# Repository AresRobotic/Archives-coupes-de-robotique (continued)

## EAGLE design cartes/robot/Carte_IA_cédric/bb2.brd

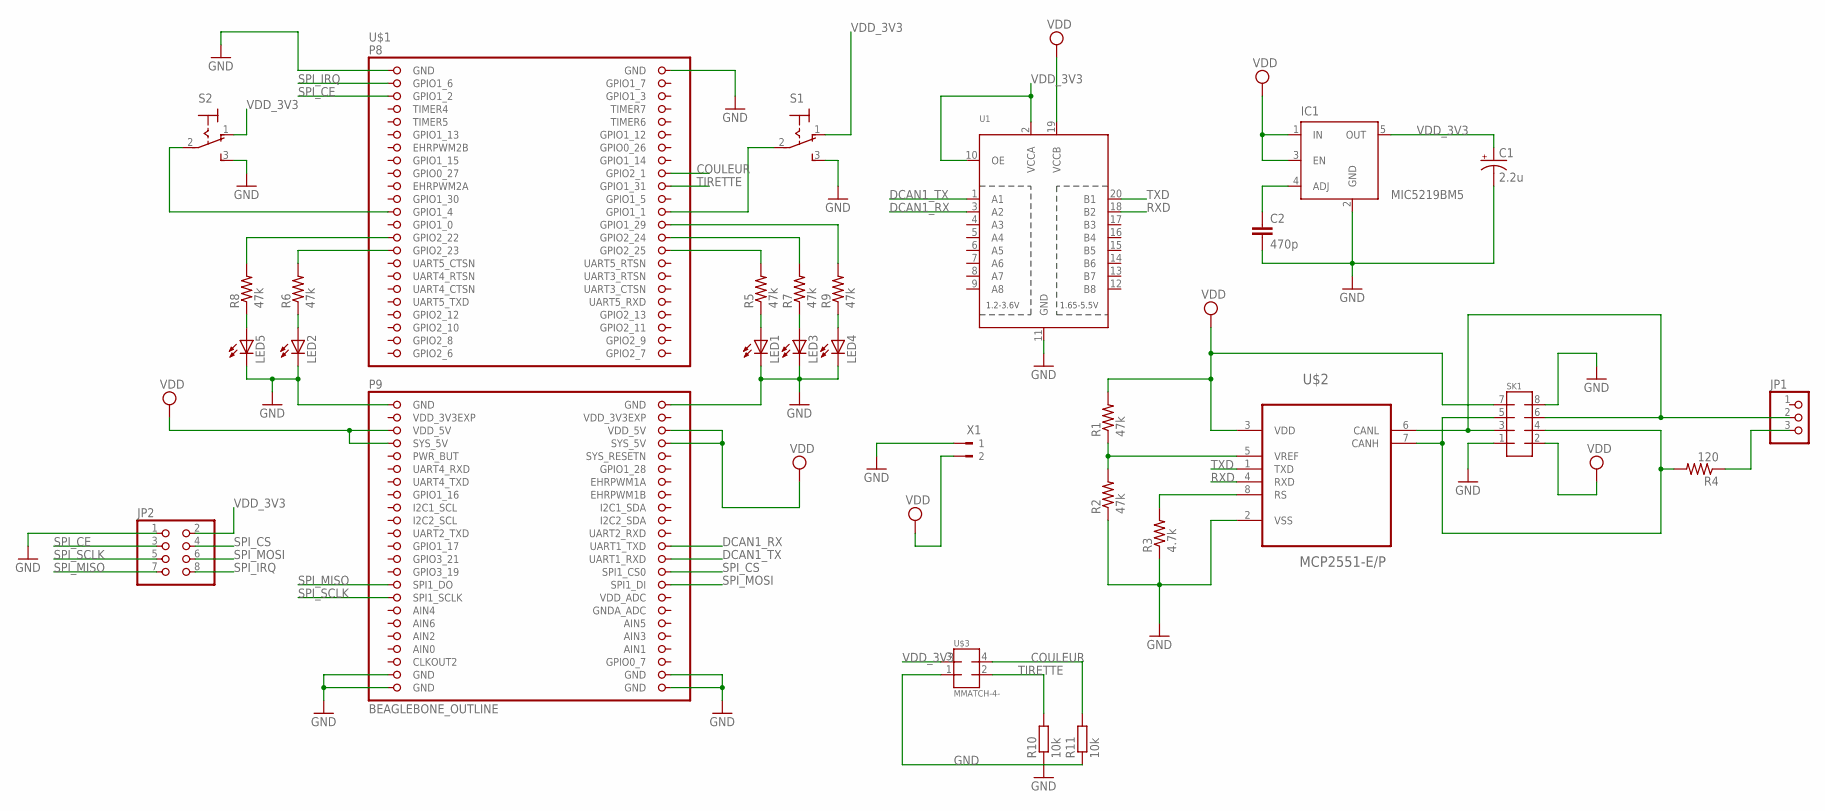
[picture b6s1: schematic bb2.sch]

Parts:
C1: 2.2u; E5-4
C2: 470p; C025-040X050
IC1: MIC5219BM5; SOT23-5
JP1: PINHD-1X3; 1X03
JP2: PINHD-2X4; 2X04
LED1, LED2, LED3, LED4, LED5: LED5MM
R1, R2, R5, R6, R7, R8, R9: 47k; 0207/9
R3: 4.7k; 0207/9
R4: 120; 0207/9
R10, R11: 10k; R0805
S1, S2: 320-916
SK1: MMATCH-8-PTH; AMP-215079-8
U1: TXB0108PWR; TSSOP20
U$1: BEAGLEBONE_OUTLINE; BEAGLEBONE_SHIELD
U$2: MCP2551-E/P; DIP254P762X432-8
U$3: MMATCH-4-; AMP-215079-4
X1: 180G-2

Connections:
AIN0: U$1.85 (AIN0)
COULEUR: R11.2, U$1.18 (GPIO2_1), U$3.4 (8)
DCAN1_RX: U1.3 (A2), U$1.70 (UART1_TXD)
DCAN1_TX: U1.1 (A1), U$1.72 (UART1_RXD)
GND: C1.-, C2.2, IC1.2 (GND), JP2.1, LED1.K (C), LED2.K (C), LED3.K (C), LED4.K (C), LED5.K (C), R2.1, R3.1, R10.1, R11.1, S1.3 (S), S2.3 (S), SK1.1, SK1.8, U1.11 (GND), U$1.1 (GND), U$1.2 (GND), U$1.47 (GND), U$1.48 (GND), U$1.89 (GND), U$1.90 (GND), U$1.91 (GND), U$1.92 (GND), U$2.2 (VSS), U$3.1 (5), X1.1
unnamed: R1.1, R2.2, U$2.5 (VREF)
unnamed: JP1.3, R4.1
unnamed: R3.2, U$2.8 (RS)
unnamed: C2.1, IC1.4 (ADJ)
unnamed: R5.2, U$1.30 (GPIO2_25)
unnamed: R6.2, U$1.29 (GPIO2_23)
unnamed: R7.2, U$1.28 (GPIO2_24)
unnamed: R9.2, U$1.26 (GPIO1_29)
unnamed: LED5.A, R8.1
unnamed: S1.2, U$1.24 (GPIO1_1)
unnamed: S2.2, U$1.23 (GPIO1_4)
unnamed: R8.2, U$1.27 (GPIO2_22)
unnamed: JP1.2, SK1.3, SK1.6, U$2.6 (CANL)
unnamed: R4.2, SK1.4, SK1.5, U$2.7 (CANH)
unnamed: LED2.A, R6.1
unnamed: LED1.A, R5.1
unnamed: LED3.A, R7.1
unnamed: LED4.A, R9.1
RXD: U1.18 (B2), U$2.4 (RXD)
SPI_CE: JP2.3, U$1.5 (GPIO1_2)
SPI_CS: JP2.4, U$1.74 (SPI1_CS0)
SPI_IRQ: JP2.8, U$1.3 (GPIO1_6)
SPI_MISO: JP2.7, U$1.75 (SPI1_DO)
SPI_MOSI: JP2.6, U$1.76 (SPI1_DI)
SPI_SCLK: JP2.5, U$1.77 (SPI1_SCLK)
TIRETTE: R10.2, U$1.20 (GPIO1_31), U$3.2 (6)
TXD: U1.20 (B1), U$2.1 (TXD)
VDD: IC1.1 (IN), IC1.3 (EN), R1.2, SK1.2, SK1.7, U1.19 (VCCB), U$1.51 (VDD_5V), U$1.52 (VDD_5V), U$1.53 (SYS_5V), U$1.54 (SYS_5V), U$2.3 (VDD), X1.2
VDD_3V3: C1.+, IC1.5 (OUT), JP2.2, S1.1 (O), S2.1 (O), U1.2 (VCCA), U1.10 (OE), U$3.3 (7)
VDD_3V3EXP: U$1.49 (VDD_3V3EXP), U$1.50 (VDD_3V3EXP)

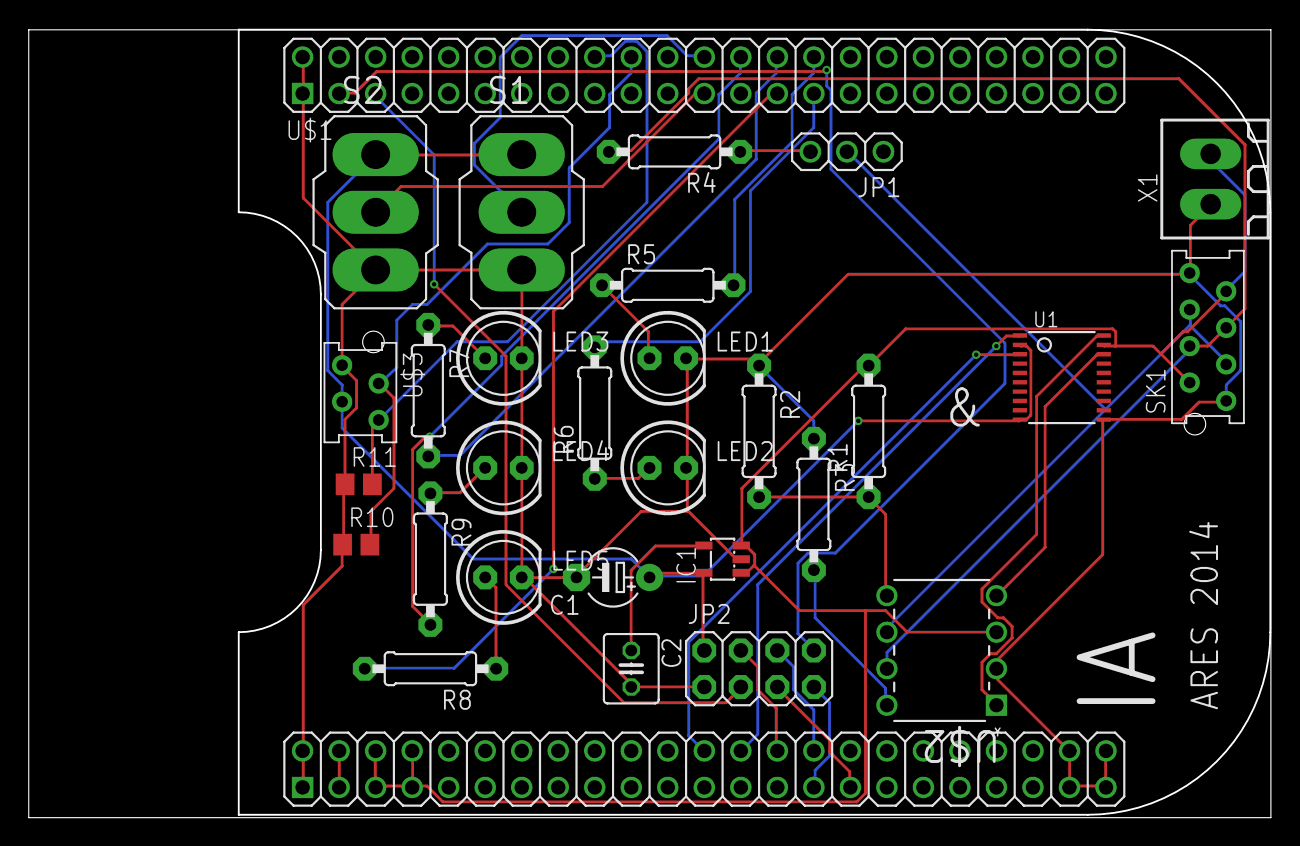
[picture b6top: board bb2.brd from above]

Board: 2 copper layers, 86.3 x 54.7 mm, 29 parts (0 on the bottom side), 34 nets.

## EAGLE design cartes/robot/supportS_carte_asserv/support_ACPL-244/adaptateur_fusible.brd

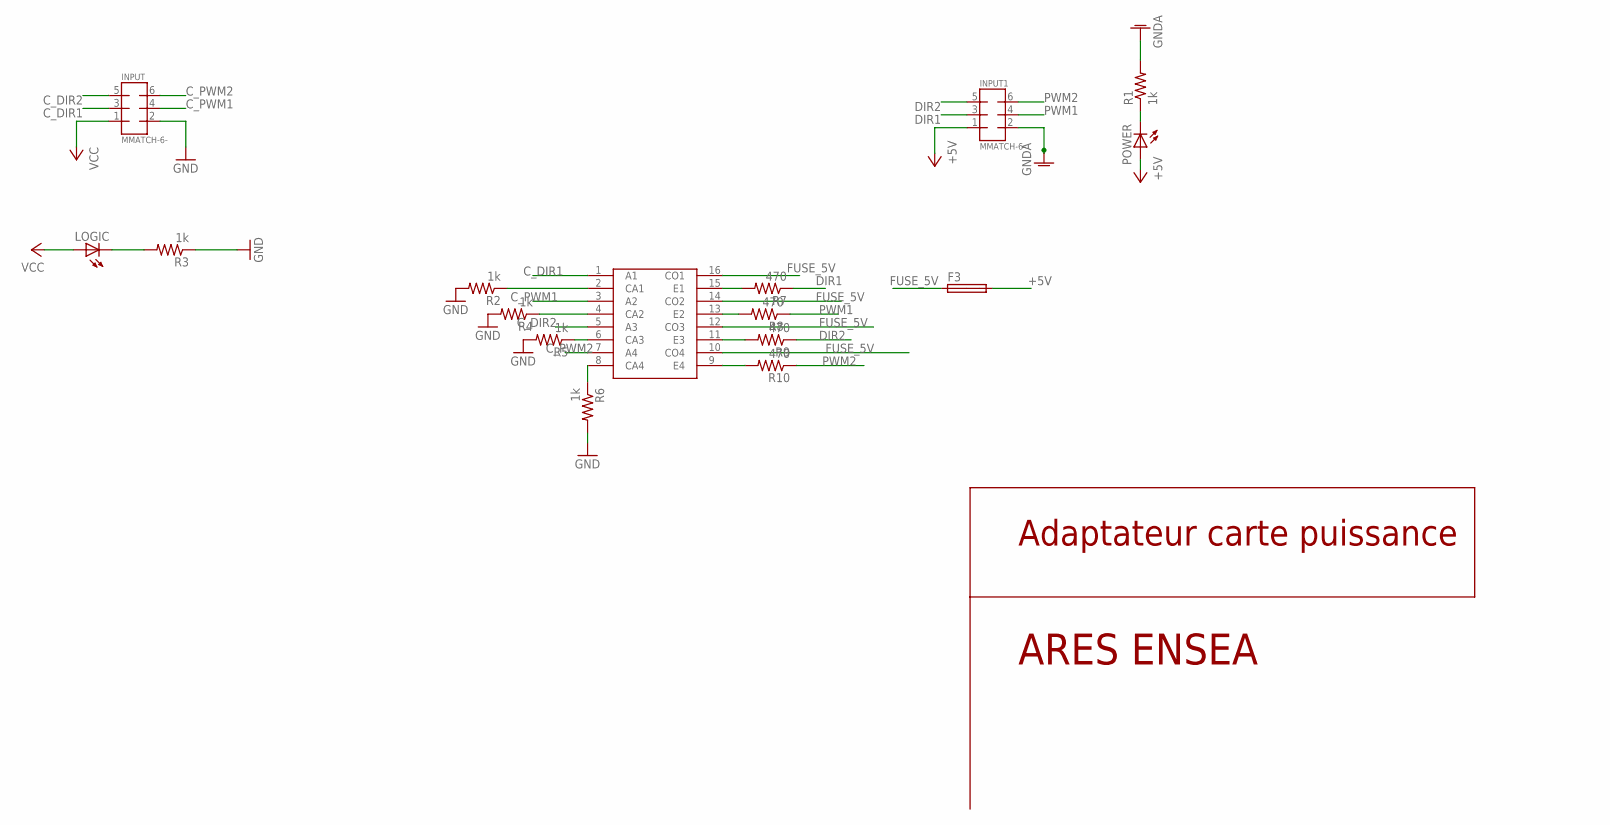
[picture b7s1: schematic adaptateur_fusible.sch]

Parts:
F3: SHK20Q
INPUT, INPUT1: MMATCH-6-; AMP-215079-6
LOGIC: LEDSML0805; SML0805
POWER: LEDSML0805; SML0805
R1, R2, R3, R4, R5, R6: 1k; M0805
R7, R8, R9, R10: 470; M0805
U$1: ACPL-244

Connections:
+5V: F3.2A, INPUT1.1 (3), POWER.A
C_DIR1: INPUT.3 (5), U$1.1 (A1)
C_DIR2: INPUT.5 (7), U$1.5 (A3)
C_PWM1: INPUT.4 (6), U$1.3 (A2)
C_PWM2: INPUT.6 (8), U$1.7 (A4)
DIR1: INPUT1.3 (5), R7.1
DIR2: INPUT1.5 (7), R9.1
FUSE_5V: F3.1A, U$1.10 (CO4), U$1.12 (CO3), U$1.14 (CO2), U$1.16 (CO1)
GND: INPUT.2 (4), R2.2, R3.1, R4.2, R5.2, R6.2
GNDA: INPUT1.2 (4), R1.2
unnamed: R9.2, U$1.11 (E3)
unnamed: R2.1, U$1.2 (CA1)
unnamed: POWER.C, R1.1
unnamed: LOGIC.C, R3.2
unnamed: R4.1, U$1.4 (CA2)
unnamed: R5.1, U$1.6 (CA3)
unnamed: R6.1, U$1.8 (CA4)
unnamed: R7.2, U$1.15 (E1)
unnamed: R8.2, U$1.13 (E2)
unnamed: R10.2, U$1.9 (E4)
PWM1: INPUT1.4 (6), R8.1
PWM2: INPUT1.6 (8), R10.1
VCC: INPUT.1 (3), LOGIC.A

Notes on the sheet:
ARES ENSEA
Adaptateur carte puissance

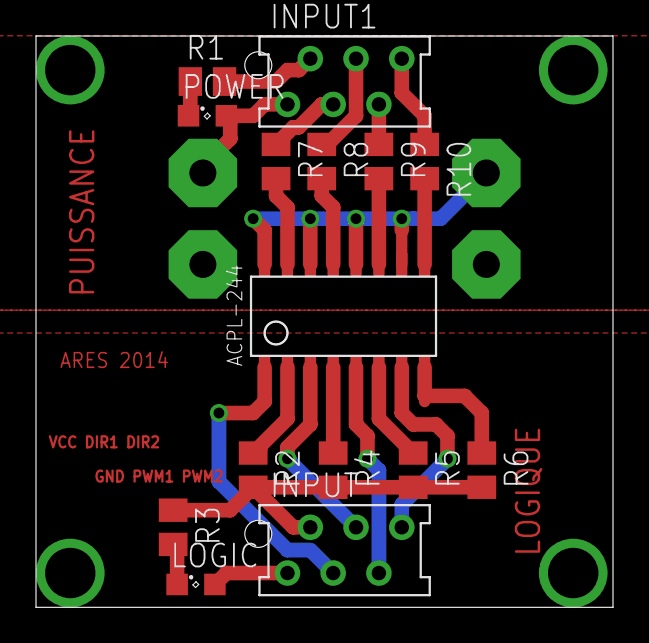
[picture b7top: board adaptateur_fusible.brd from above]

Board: 2 copper layers, 31.9 x 31.6 mm, 16 parts (1 on the bottom side), 23 nets.

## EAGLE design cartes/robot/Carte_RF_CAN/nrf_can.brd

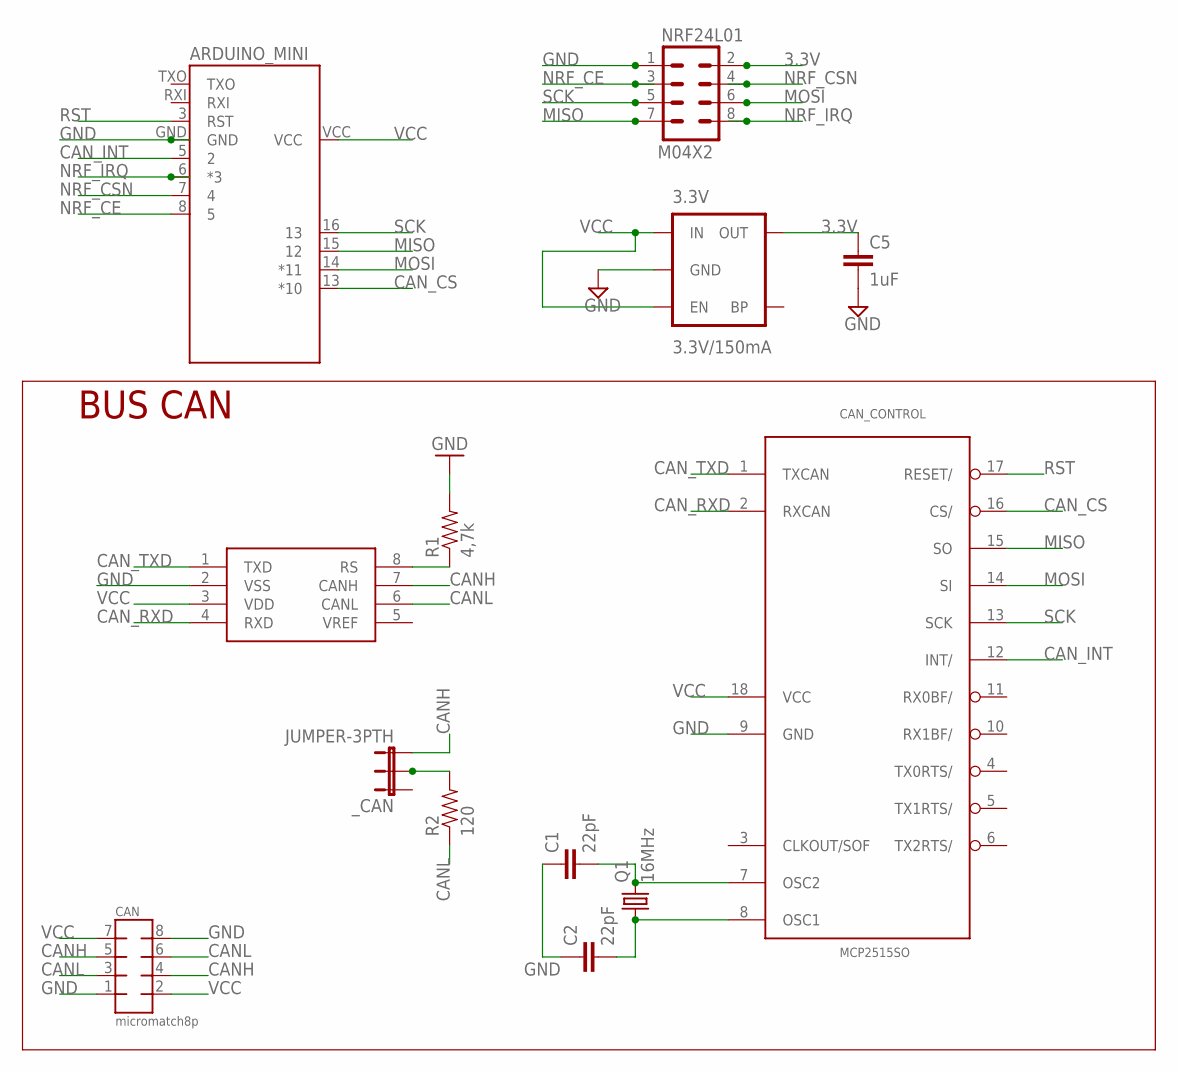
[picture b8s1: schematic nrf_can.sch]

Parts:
3.3V: 3.3V/150mA; SOT23-5
ARDUINO_MINI: ARDUINO_PRO_MININRF24L01; ARDUINO_PRO_MINI
C1, C2: 22pF; 0805
C5: 1uF; 0805
CAN: micromatch8p; AMP-215079-8
CAN_CONTROL: MCP2515SO; SO18L
NRF24L01: M04X2; 2X4
Q1: 16MHz; HC49/S
R1: 4,7k; 0805
R2: 120; 0805
TRANSCEIVER: MCP2551; SO08
_CAN: JUMPER-3PTH; 1X03

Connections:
3.3V: 3.3V.5 (OUT), C5.1, NRF24L01.2
CANH: CAN.4, CAN.5, TRANSCEIVER.7 (CANH), _CAN.3
CANL: CAN.3, CAN.6, R2.1, TRANSCEIVER.6 (CANL)
CAN_CS: ARDUINO_MINI.13 (*10), CAN_CONTROL.16 (CS/)
CAN_INT: ARDUINO_MINI.5 (2), CAN_CONTROL.12 (INT/)
CAN_RXD: CAN_CONTROL.2 (RXCAN), TRANSCEIVER.4 (RXD)
CAN_TXD: CAN_CONTROL.1 (TXCAN), TRANSCEIVER.1 (TXD)
GND: 3.3V.2 (GND), ARDUINO_MINI.GND, C1.1, C2.1, C5.2, CAN.1, CAN.8, CAN_CONTROL.9 (GND), NRF24L01.1, R1.2, TRANSCEIVER.2 (VSS)
MISO: ARDUINO_MINI.15 (12), CAN_CONTROL.15 (SO), NRF24L01.7
MOSI: ARDUINO_MINI.14 (*11), CAN_CONTROL.14 (SI), NRF24L01.6
unnamed: C1.2, CAN_CONTROL.7 (OSC2), Q1.2
unnamed: C2.2, CAN_CONTROL.8 (OSC1), Q1.1
unnamed: R1.1, TRANSCEIVER.8 (RS)
unnamed: R2.2, _CAN.2
NRF_CE: ARDUINO_MINI.8 (5), NRF24L01.3
NRF_CSN: ARDUINO_MINI.7 (4), NRF24L01.4
NRF_IRQ: ARDUINO_MINI.6 (*3), NRF24L01.8
RST: ARDUINO_MINI.3 (RST), CAN_CONTROL.17 (RESET/)
SCK: ARDUINO_MINI.16 (13), CAN_CONTROL.13 (SCK), NRF24L01.5
VCC: 3.3V.1 (IN), 3.3V.3 (EN), ARDUINO_MINI.VCC, CAN.2, CAN.7, CAN_CONTROL.18 (VCC), TRANSCEIVER.3 (VDD)

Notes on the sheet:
BUS CAN

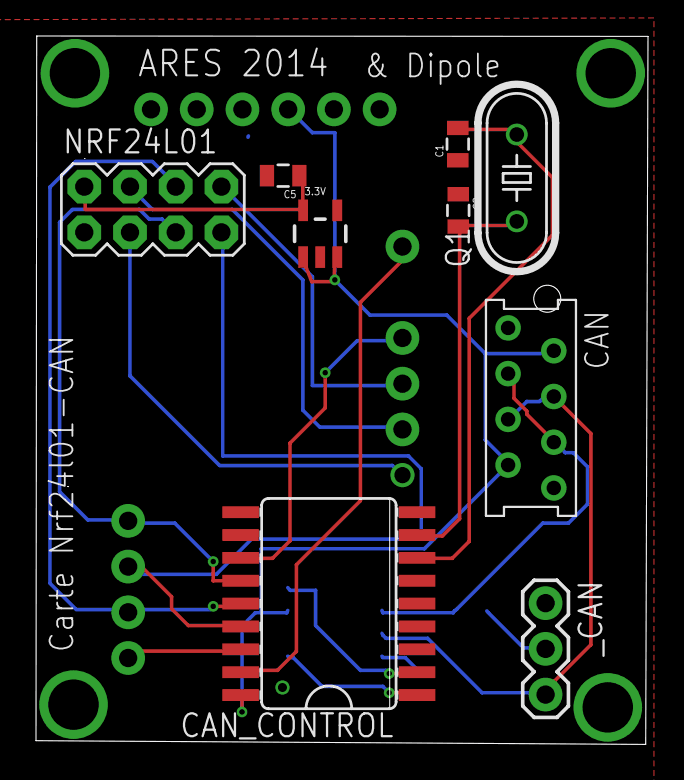
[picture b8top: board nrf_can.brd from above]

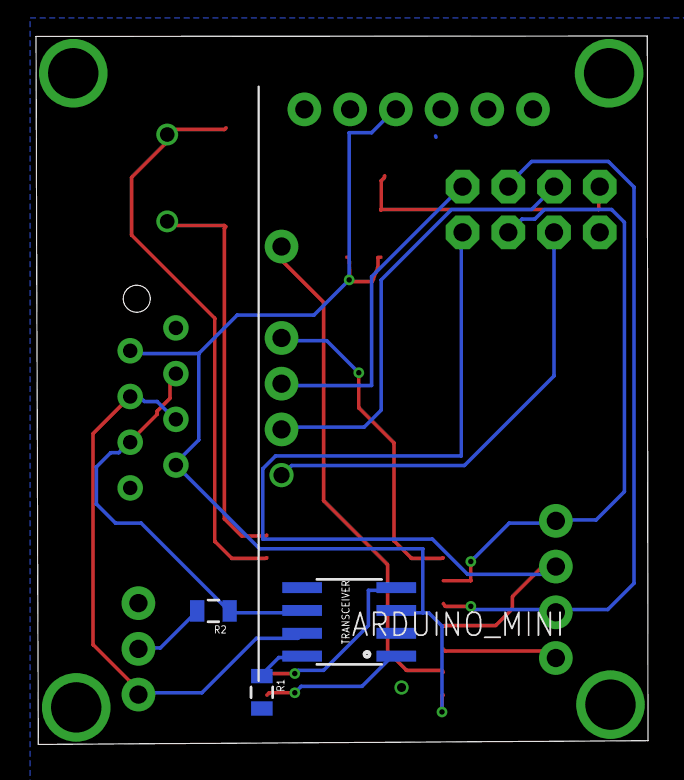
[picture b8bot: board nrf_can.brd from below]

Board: 2 copper layers, 34.0 x 39.4 mm, 13 parts (4 on the bottom side), 20 nets.

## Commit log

2014-04-20 carte asservissement
2014-04-20 carte puissance
2014-04-21 Ajout carte servo et sharp
2014-04-21 carte plan B
2014-04-21 new version + gerber test
2014-04-21 oubli du drill
2014-04-21 nouvelle version
    piste plus large pour le 12V
2014-04-21 nouvelle version nouveau jumper
2014-04-21 nouveau gerber
2014-04-23 divers
2014-04-23 finit rf
2014-04-23 Ajout dru et finit carte
2014-04-23 ajout erreurs
2014-04-23 config gerber
2014-04-23 ajout gerber
2014-04-24 carte ia
2014-04-24 Ajout carte sharp v2
2014-04-24 wait
2014-04-24 end sharp
2014-04-24 ajout nvlle carte puissance
2014-04-24 Ajout carte RF avec bon fichier
2014-04-24 Ajout carte puissance
2014-04-24 end puissance
2014-04-24 nouvelle IA
2014-04-24 JAUNE
2014-04-24 what ?
    whwhwh
2014-04-24 delete
2014-04-24 add old version of IA
2014-04-24 servo
2014-04-25 Ajout carte bouton
2014-04-25 ajouts carte puissance
2014-04-25 renomage carte clem
2014-04-25 ajout logos
2014-04-25 plein de trucs
2014-04-25 lot of things
2014-04-25 ajouts problemes
2014-04-25 merge
2014-04-26 Ajout carte alim et corrections à effectuer
2014-04-26 sharp
2014-04-26 nouvelles cartes à jour
2014-04-26 Merge branch 'master' of https://github.com/AresRobotic/Robot-2013-2014
    Conflicts:
    cartes/Carte plan B/README.txt
    cartes/Carte_bouton/README.txt
    cartes/servo_shield/README.txt
    cartes/sharp_shield/README.txt
    cartes/sharp_shield/mini_board0.brd
2014-04-27 Ajout des readme supprimés par Cédric
2014-04-27 ajout carte Simond
2014-04-27 remarques alim
2014-04-27 carte bouton v2
2014-04-27 réorganisation des fichiers
2014-04-28 modif carte puissance
2014-04-28 ajout brd carte ia supprimé par Cédric
2014-04-28 nouvelle version carte IA
    correction bug piste trop près du détrompeur
2014-04-28 ajout logo et correction espacement piste
2014-04-28 new dipole gerber
2014-04-28 rererererer
2014-04-28 ajout gerber puissance + export wiki
2014-04-28 whatt ?
2014-05-01 Create alim_01_05
    pas de plan de masse, pas de chgt de header.
2014-05-01 pas de plans de masse, pas de chgt de header
2014-05-08 testgit
2014-05-08 Revert "testgit"
    This reverts commit 06fa61906e726527d93af0c4958ef9da74c90b20.
2014-05-09 Carte puissance vENSEA
2014-05-12 Maj carte puissance vENSEA + correction bug + modif carte RF-CAN
2014-05-12 close #6
    ajout des résistances pull-up
2014-05-12 Ajout du code de l'ascenseur
2014-05-12 ajout carte alim
2014-05-12 Fix du bug #5 avec l'ajout d'un treansceiver RS485 pour l'ax12
2014-05-12 ajout fichiers intermediaire
2014-05-13 ajout lib can arduino
2014-05-14 test
2014-05-14 Ajout dernieres modif carte alim
2014-05-15 ajout carte routée
2014-05-17 ajout carte lanceur de balle
2014-05-17 ajout cartes à envoyer
2014-05-17 nouveaux gerber
2014-05-17 carte nrf-cAN gerber
2014-05-17 a envoyer
2014-05-18 carte mos pwm modifié
2014-05-18 ascenseur
2014-05-18 Modif carte rf avec erreur vue par Pak
2014-05-18 Modif carte sharp et carte servo avec probleme transceiver
2014-05-18 version du 18 + librairies
    ajout de la nouvelle version, avec les plans de masses + lbr ptn et
    murata
2014-05-18 Ajout de la carte ascenseur
2014-05-18 Correction de la carte ascenseur
2014-05-18 Correction
    Ajout de la connexion à l'alim 'dirty' et d'un LM7805 pour faire du 5V
    dirty au cas où.
2014-05-18 Correction carte ascenseur
    Ajout des leds d'indication de présence de tension, 5V, 5V dirty, 12V
    dirty
2014-05-18 Carte ascenseur
    Correction d'une erreur dans la schéma, début du routage.
2014-05-19 Ajout carte ultrason et génération pdf
2014-05-19 alim sans murata
2014-05-20 Maj ascenseur
2014-05-20 modif carte ascensseur
2014-05-21 correction carte alim
2014-05-21 Il y avait trop de dossier, ça me soulait !
2014-05-22 Ajout carte support sharp
2014-05-22 modif script
2014-05-22 Il ne faut pas faire des modif à 3h du mat...
2014-05-24 Maj code Ascenseur
    Ajout des code de test des différents modules
2014-05-24 Maj (bug git)
2014-05-24 azerty
2014-05-25 nettoyage + ajout carte fusible pour la puissance
2014-05-25 Changement dossier
2014-05-25 ajout carte ascensseur v2 avec capa découplage, fusible et UART
2014-05-25 old file
2014-05-25 Maj carte ascenseur
    Fusible, condo d'alim, jumper triple pour l'alim 5V, LED pour le PIC,
    sortie UART
2014-05-25 Maj carte ascenseur
    2 via moins
2014-05-25 change isolate, airwaves qui en découlaient de ce changement, épaisseur sérigraphie et sérigraphie de certains composants
2014-05-25 Maj code
2014-05-26 Ajout carte adaptation acpl-244 (à router)
2014-05-26 thunmb
2014-05-26 routage adaptateur
2014-05-27 Ajout nvlle carte opto
2014-05-28 nouvelle carte sans ne555
2014-06-26 modification arborescence git
2014-06-26 annulation de conneries
2014-06-27 nouvelle archi
2014-06-27 mov eto Robot-2013-2014
